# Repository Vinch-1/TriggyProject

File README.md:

# TriggyProject
Shared files of the Triggy project

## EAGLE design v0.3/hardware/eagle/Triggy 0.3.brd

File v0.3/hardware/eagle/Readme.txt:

These files can be directly read with EagleCAD software.
Triggy.lbr is the library containing the footprint for specific components.

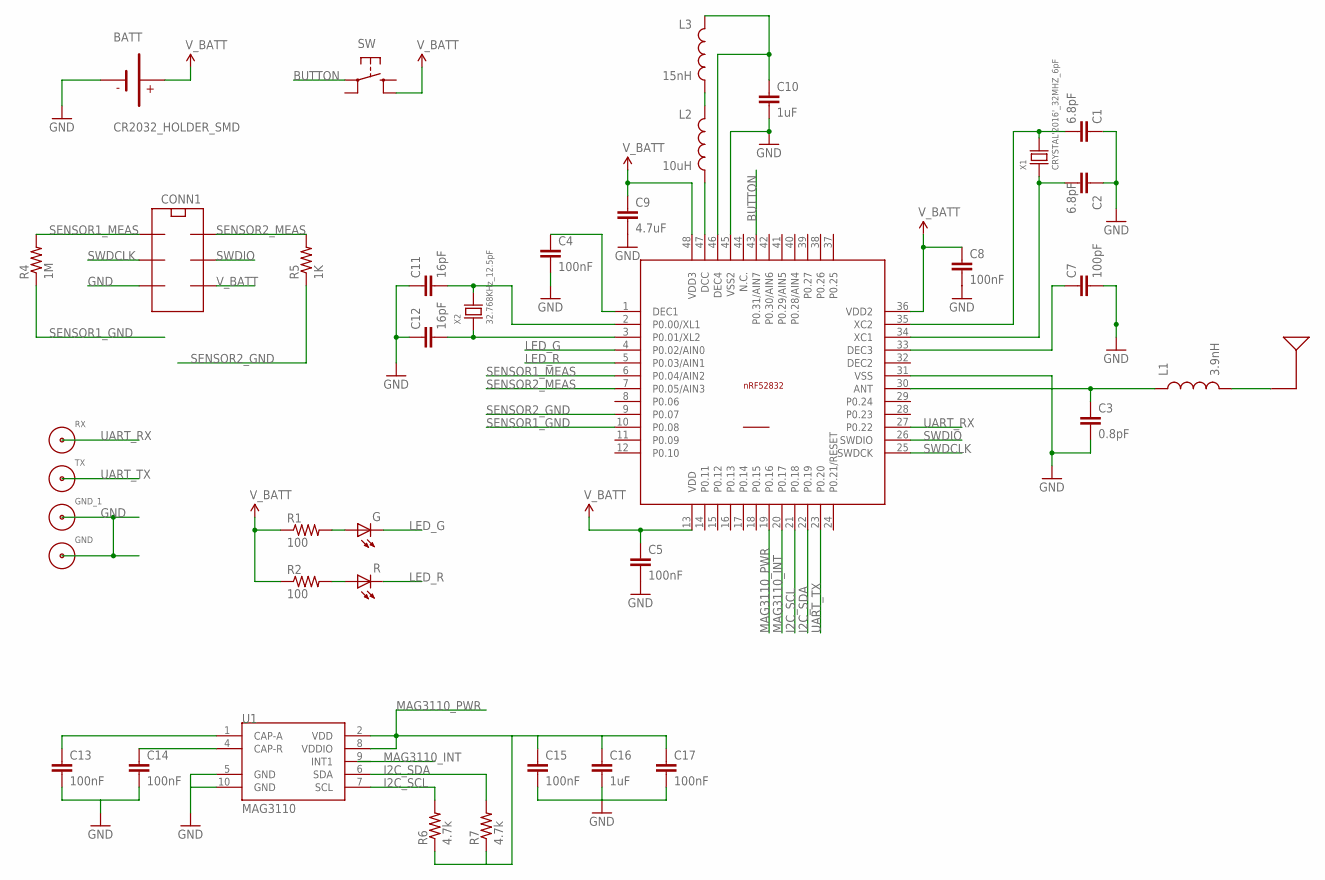
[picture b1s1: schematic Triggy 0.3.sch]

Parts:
ANT: ANTENNA_2450AT43A100; ANTENNA-SMD-7MM
BATT: CR2032_HOLDER_SMD
C1, C2: 6.8pF; 0402-CAP
C3: 0.8pF; 0402-CAP
C4, C5, C8, C13, C14, C15, C17: 100nF; 0402-CAP
C7: 100pF; 0402-CAP
C9: 4.7uF; 0603-CAP
C10, C16: 1uF; 0603-CAP
C11, C12: 16pF; 0402-CAP
CONN1: MOLEX_8734006XX
GND: SINGLE_CONN; SINGLE-CONN
GND_1: SINGLE_CONN; SINGLE-CONN
L1: 3.9nH; C0402
L2: 10uH; 0603
L3: 15nH; C0402
LEDS: LED-R-G; LED-RG-SMD-3X2.5MM
NRF52832: NRF52832_QFN; QFN48
R1, R2: 100; 0402-RES
R4: 1M; 0402-RES
R5: 1K; 0402-RES
R6, R7: 4.7k; 0402-RES
RX: SINGLE_CONN; SINGLE-CONN
SW: SWITCH-PANASONIC
TX: SINGLE_CONN; SINGLE-CONN
U1: MAG3110; DFN-10
X1: CRYSTAL'2016'_32MHZ_6pF; X4-SMD-2.0X1.6MM
X2: 32.768KHz_12.5pF; X2-SMD-3.2X1.5MM

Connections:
BUTTON: NRF52832.43 (P0.31/AIN7), SW.A (1)
DEC2: NRF52832.32 (DEC2)
GND: BATT.-, C1.1, C2.1, C3.2, C4.2, C5.2, C7.2, C8.2, C9.2, C10.2, C11.1, C12.1, C13.2, C14.2, C15.2, C16.2, C17.2, CONN1.P$5, GND.1, GND_1.1, NRF52832.31 (VSS), NRF52832.45 (VSS2), U1.5 (GND), U1.10 (GND)
I2C_SCL: NRF52832.21 (P0.18), R6.2, U1.7 (SCL)
I2C_SDA: NRF52832.22 (P0.19), R7.2, U1.6 (SDA)
LED_G: LEDS.P$4 (P4), NRF52832.4 (P0.02/AIN0)
LED_R: LEDS.P$2 (P2), NRF52832.5 (P0.03/AIN1)
MAG3110_INT: NRF52832.20 (P0.17), U1.9 (INT1)
MAG3110_PWR: C15.1, C16.1, C17.1, NRF52832.19 (P0.16), R6.1, R7.1, U1.2 (VDD), U1.8 (VDDIO)
unnamed: C3.1, L1.1, NRF52832.30 (ANT)
unnamed: ANT.1, L1.2
unnamed: C1.2, NRF52832.35 (XC2), X1.4 (2)
unnamed: C7.1, NRF52832.33 (DEC3)
unnamed: C4.1, NRF52832.1 (DEC1)
unnamed: C2.2, NRF52832.34 (XC1), X1.2 (1)
unnamed: L2.1, L3.2
unnamed: C12.2, NRF52832.3 (P0.01/XL2), X2.P$1 (1)
unnamed: C11.2, NRF52832.2 (P0.00/XL1), X2.P$2 (2)
unnamed: L2.2, NRF52832.47 (DCC)
unnamed: C13.1, U1.1 (CAP-A)
unnamed: C14.1, U1.4 (CAP-R)
unnamed: C10.1, L3.1, NRF52832.46 (DEC4)
unnamed: LEDS.P$3 (P3), R1.2
unnamed: LEDS.P$1 (P1), R2.2
SENSOR1_GND: NRF52832.10 (P0.08), R4.1
SENSOR1_MEAS: CONN1.P$1, NRF52832.6 (P0.04/AIN2), R4.2
SENSOR2_GND: NRF52832.9 (P0.07), R5.1
SENSOR2_MEAS: CONN1.P$2, NRF52832.7 (P0.05/AIN3), R5.2
SWDCLK: CONN1.P$3, NRF52832.25 (SWDCK)
SWDIO: CONN1.P$4, NRF52832.26 (SWDIO)
UART_RX: NRF52832.27 (P0.22), RX.1
UART_TX: NRF52832.23 (P0.20), TX.1
V_BATT: BATT.+, BATT.+@ (+), C5.1, C8.1, C9.1, CONN1.P$6, NRF52832.13 (VDD), NRF52832.36 (VDD2), NRF52832.48 (VDD3), R1.1, R2.1, SW.B' (4)

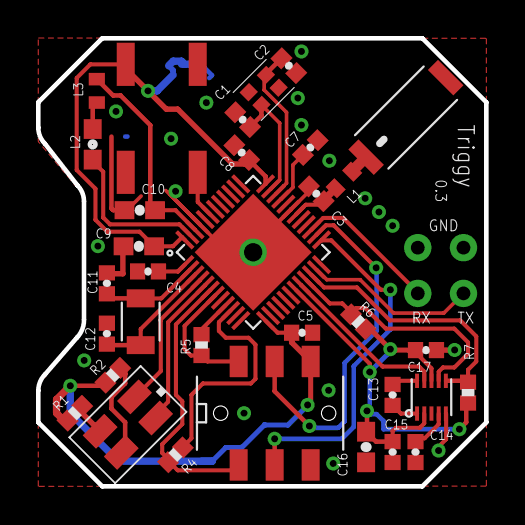
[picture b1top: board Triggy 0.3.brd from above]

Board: 2 copper layers, 24.9 x 24.9 mm, 38 parts (1 on the bottom side), 32 nets.

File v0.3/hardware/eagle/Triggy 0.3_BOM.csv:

"Part";"Value";"Device";"Package";"Description";"";
"ANT";"ANTENNA_2450AT43A100";"ANTENNA_2450AT43A100";"ANTENNA-SMD-7MM";"";"";
"BATT";"CR2032_HOLDER_SMD";"CR2032_HOLDER_SMD";"CR2032_HOLDER_SMD";"";"";
"C1";"6.8pF";"CAP0402-CAP";"0402-CAP";"Capacitor";"";
"C2";"6.8pF";"CAP0402-CAP";"0402-CAP";"Capacitor";"";
"C3";"0.8pF";"CAP0402-CAP";"0402-CAP";"Capacitor";"";
"C4";"100nF";"CAP0402-CAP";"0402-CAP";"Capacitor";"";
"C5";"100nF";"CAP0402-CAP";"0402-CAP";"Capacitor";"";
"C7";"100pF";"CAP0402-CAP";"0402-CAP";"Capacitor";"";
"C8";"100nF";"CAP0402-CAP";"0402-CAP";"Capacitor";"";
"C9";"4.7uF";"CAP0603-CAP";"0603-CAP";"Capacitor";"";
"C10";"1uF";"CAP0603-CAP";"0603-CAP";"Capacitor";"";
"C11";"16pF";"CAP0402-CAP";"0402-CAP";"Capacitor";"";
"C12";"16pF";"CAP0402-CAP";"0402-CAP";"Capacitor";"";
"C13";"100nF";"CAP0402-CAP";"0402-CAP";"Capacitor";"";
"C14";"100nF";"CAP0402-CAP";"0402-CAP";"Capacitor";"";
"C15";"100nF";"CAP0402-CAP";"0402-CAP";"Capacitor";"";
"C16";"1uF";"CAP0603-CAP";"0603-CAP";"Capacitor";"";
"C17";"100nF";"CAP0402-CAP";"0402-CAP";"Capacitor";"";
"CONN1";"MOLEX_8734006XX";"MOLEX_8734006XX";"MOLEX_8734006XX";"";"";
"GND";"SINGLE_CONN";"SINGLE_CONN";"SINGLE-CONN";"";"";
"GND_1";"SINGLE_CONN";"SINGLE_CONN";"SINGLE-CONN";"";"";
"L1";"3.9nH";"INDUCTOR0402";"C0402";"Inductors";"";
"L2";"10uH";"INDUCTOR0603";"0603";"Inductors";"";
"L3";"15nH";"INDUCTOR0402";"C0402";"Inductors";"";
"LEDS";"LED-R-G";"LED-R-G";"LED-RG-SMD-3X2.5MM";"";"";
"NRF52832";"NRF52832_QFN";"NRF52832_QFN";"QFN48";"";"";
"R1";"100";"RESISTOR0402";"0402-RES";"Resistor";"";
"R2";"100";"RESISTOR0402";"0402-RES";"Resistor";"";
"R4";"1M";"RESISTOR0402";"0402-RES";"Resistor";"";
"R5";"1K";"RESISTOR0402";"0402-RES";"Resistor";"";
"R6";"4.7k";"RESISTOR0402";"0402-RES";"Resistor";"";
"R7";"4.7k";"RESISTOR0402";"0402-RES";"Resistor";"";
"RX";"SINGLE_CONN";"SINGLE_CONN";"SINGLE-CONN";"";"";
"SW";"SWITCH-PANASONIC";"SWITCH-PANASONIC";"SWITCH-PANASONIC";"";"";
"TX";"SINGLE_CONN";"SINGLE_CONN";"SINGLE-CONN";"";"";
"U1";"MAG3110";"MAG3110";"DFN-10";"3-axis digital (I2C) magnetometer";"";
"X1";"CRYSTAL'2016'_32MHZ_6pF";"CRYSTAL'2016'_32MHZ";"X4-SMD-2.0X1.6MM";"";"";
"X2";"32.768KHz_12.5pF";"CRYSTAL'3215'";"X2-SMD-3.2X1.5MM";"";"";

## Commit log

2017-05-09 Rename hardware/eagle/readme.txt to v0.1/hardware/eagle/readme.txt
2017-05-09 Rename hardware/eagle/Triggy.lbr to v0.1/hardware/eagle/Triggy.lbr
2017-05-09 Rename hardware/eagle/Triggy 0.1.sch to v0.1/hardware/eagle/Triggy 0.1.sch
2017-05-09 Rename hardware/eagle/Triggy 0.1.brd to v0.1/hardware/eagle/Triggy 0.1.brd
2017-05-09 Rename hardware/eagle/Triggy 0.1 BOM.csv to v0.1/hardware/eagle/Triggy 0.1 BOM.csv

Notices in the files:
parts and their libraries:
SparkFun-Capacitors: Licensing: Creative Commons ShareAlike 4.0 International - https://creativecommons.org/licenses/by-sa/4.0
